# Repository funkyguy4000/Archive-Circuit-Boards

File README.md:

## This is an inactive repository used for archival purposes only
### Most of these designs and libraries were created while I was at university

#Circuit-Boards

A collection of my circuit boards and devices

##Strutz Library.lbr 
###This is a collection the parts I've made.  Some of the packages are copied from other libraries.
I'll list the important devices here:

Device | Package 1 | Package 2 | Package 3 | Description 
| --- | --- | --- | --- | --- |
**25AA1024**  |  DFN8-5x6 | 8-PDIP | SO8 | 1MBit SPI EEPROM from Microchip
**74AVC8T245** | QFN-60 | TSSOP-48 | | 8-biit logic level converter from NXP
**AD1939**  |  QFP64  | | | 4 ADC/ 8 DAC, 192 kHz, 24-Bit codec from Analog Devices
**ADP5589**  | 24-LFCSP (QFN) | 25-WLCSP (BGA) | | Keypad decoder / 19-bit IO Expander from Analog Devices
**ADSP-21479** | QFN-88 | | | SHARC DSP processor from Analog Devices
**ADSP-21483/6/7/9** | LQFP-176 | | | SHARC DSP processsor from analog devices
**AS1130** | TSSOP-28 | WL_CSP-20 (BGA) | | 132 LED driver from austriamicrosystems 
**AS3935** | QFN-16 | | | Lightning Sensor from austriamicrosystems
**AT25128B/256B** | 8VBGA | | | 128k/256k SPI EEPROM from Atmel
**ATMEGA8U2** | QFN-32 | | | 8-bit AVR microcontroller with embedded USB and 8kB flash from Atmel
**ATMEGA16** | 40-PDIP | | | 8-bit AVR microcontroller with 16kB flash from Atmel
**ATTINY4/5/6/9/10** | SOT-23-6 | | | 8-bit AVR micrcontroller for tiny applications from Atmel
**BGF120A** | TSLP-4-8 | | | Dual channel, ultra-low capacitance ESD diode from Infineon
**CS4234** | QFN-40 | | | 4 ADC/ 5 DAC Codec with programmable class H driver from Cirrus Logic
**CS4344** | TSSOP-10 | | | 24-bit, 192kHz Stereo DAC from Cirrus Logic
**CS5343** | TSSOP-10 | | | 24-bit Stereo ADC from Cirrus Logic
**CS42436** | QFP-52 | | | 6 ADC/ 6 DAC, 192kHz TDM audio codec from Cirrus Logic
**DS1077** | TSSOP-8 | | | Dual-programmable oscillator from Maxim
**FRDM-KL26Z**  | | | |  ***NOT TO BE USED FOR LAYOUT*** Only schematic purposes
**FT221X** | 20-QFN | 20-SSOP | | USB to FT1248 bridge from FTDI
**FT234XD** | DFN12-3x3 | | | USB to basic UART bridge from FTDI
**HIH-6130** | SO-8 | | | Digital humidity / temperature sensor from Honeywell
**HMC5983** | QFN-16 | | | 3-Axis digital compass from Honeywell
**L3GD20TR** | LGA-16 | | | 3-Axis digital gyroscope from ST Microelectronics
**LIS3MDL** | LGA-12 | | | 3-Axis digital magnetic sensor from ST Microelectronics
**LSM303DLHC** | LGA-14 | | | 3D accelerometer and 3D magnetometer from ST Microelectronics
**LT8500** | QFN-56 | | | 48-Channel LED PWM Generator with 12-bit resolution and 50MHz cascadeable serial interface from Linear Technologies
**LTC3539** | DFN8-3x3 | | | 2A, 1MHz/2MHz Synchronous Boost DC/DC Converter from Linear Technologies
**LTC3605** | QFN24 | | | 15V, 5A Synchronouse Buck Regulator from Linear Technologies
**LTC3811** | QFN38 | | | High Speed Dual, Multi-phase Buck DC/DC Controller from Linear Technologies
**M24M01** | BGA-8 | | | 1MBit I2C EEPROM from ST Microelectronics
**MCP2210** | QFN-20 | SSOP-20 | | USB to SPI bridge with GPIO from Microchip
**MMA8453Q** | QFN-16 | | | 3-Axis 10-bit/8-bit Digital Accelerometer from Freescale Semiconductor
**MMBT3904** | SOT-23 | | | 40V NPN small signal transistor
**MT48LC4M16A2** | TSOP-54 | | | 64MB x4 SDRAM from Micron
**OP275** | SO-8 | | | Bipolar/JFET Dual audio op-amp from Analog Devices
**PMOD** | 2x6 .1" Header | | | Custom part for PMOD breakout **UNTESTED**
**PT15** | 1206 | | | Phototransistor from Everlight
**RCA_Double** | Custom | | | Unkown
**SJ1-3514-SMT** | Custom | | |  Squarish Audio connector with tip switch from CUI Inc.  
**SJ3524** | Custom | | | Rectangular Audio connector with tip switch from CUI Inc
**TLC5940** | DIL28-3 | QFN-32 | TSSOP28-GROUNDPAD | 16-Channel LED driver with PWM control from Texas Instruments
**TLC5947** | QFN-32  | | | 24-Channel LED driver with PWM control from Texas Instruments
**TLC5958** | QFN-56 | | | 48-Channel LED driver with PWM control and 48kBit SRAM from Texas Instruments
**TPS62130A** | QFN16-3x3 | | | 3-17V 3A Buck DC/DC converter from Texas Instruments
**TPS84320** | RUQ_47(QFN) | | | 4.5-14.5V 3A Buck DC/DC converter from Texas Instruments
**TS3USB221** | 10-QFN | 10-SON  | | USB-2.0HS 1:2 Mux/Demux switch from Texas Instruments
**USB5534B** | QFN-64 | | | 4-Port SS/HS USB hub controller from Microchip
**USBA-DOUBLE** | Custom | | | Unknown
**WS2812-5050** | Custom | | | RGB LED driver with integrated WS2812 LED driver from Unknown
**XS1-L8A-128** | QFN-124 | | | 8-Core 32-Bit Microcontroller with 128kB SRAM from XMOS 
**XS1-U8A-128** | BGA-217 | | | 8-Core 32-Bit Microcontroller with USB Phy from XMOS
**XTAG-2** | MOLEX-52745-2097 | | | Proprietary debug adapter for XMOS devices

##On to the boards!

* **ADSP-21477...** - Breaks out the 88-QFN package of this DSP from Analog Devices
* **CS4344**  - Breaks out this Analog to Digital Converter from Cirrus
* **CS5343**  - Breaks out this Digital to Analog Converter from Cirrus
* **TLC5947 Old** - A board from when I used to layout without using a schematic.  Uses two TLC5947 ICs to manage 16 5050 RGB LEDS
* **Lego type WS2812** - A modular LED board made to connect to other pieces to make any LED display
* **Neopixel** - My board made after the Neopixel from Adafruit
* **Version 1 WS2812** - A square board using the WS2812 LEDs to make an LED matrix
* **Smod Boards** - These boards were made for half fun and half the University of Wisconsin - Stout IEEE
* **Stout IEEE Dev Board** - This is a development board in the form of an Arduino based off of the ATmega16 for UW-Stout IEEE.  Includes onboard programming based off of an ATtiny45.

More projects and such will be added soon.  I pretty much make a new one everyday.

<br />This work is licensed under a <a rel="license" href="http://creativecommons.org/licenses/by-sa/3.0/us/">Creative Commons Attribution-ShareAlike 3.0 United States License</a>.

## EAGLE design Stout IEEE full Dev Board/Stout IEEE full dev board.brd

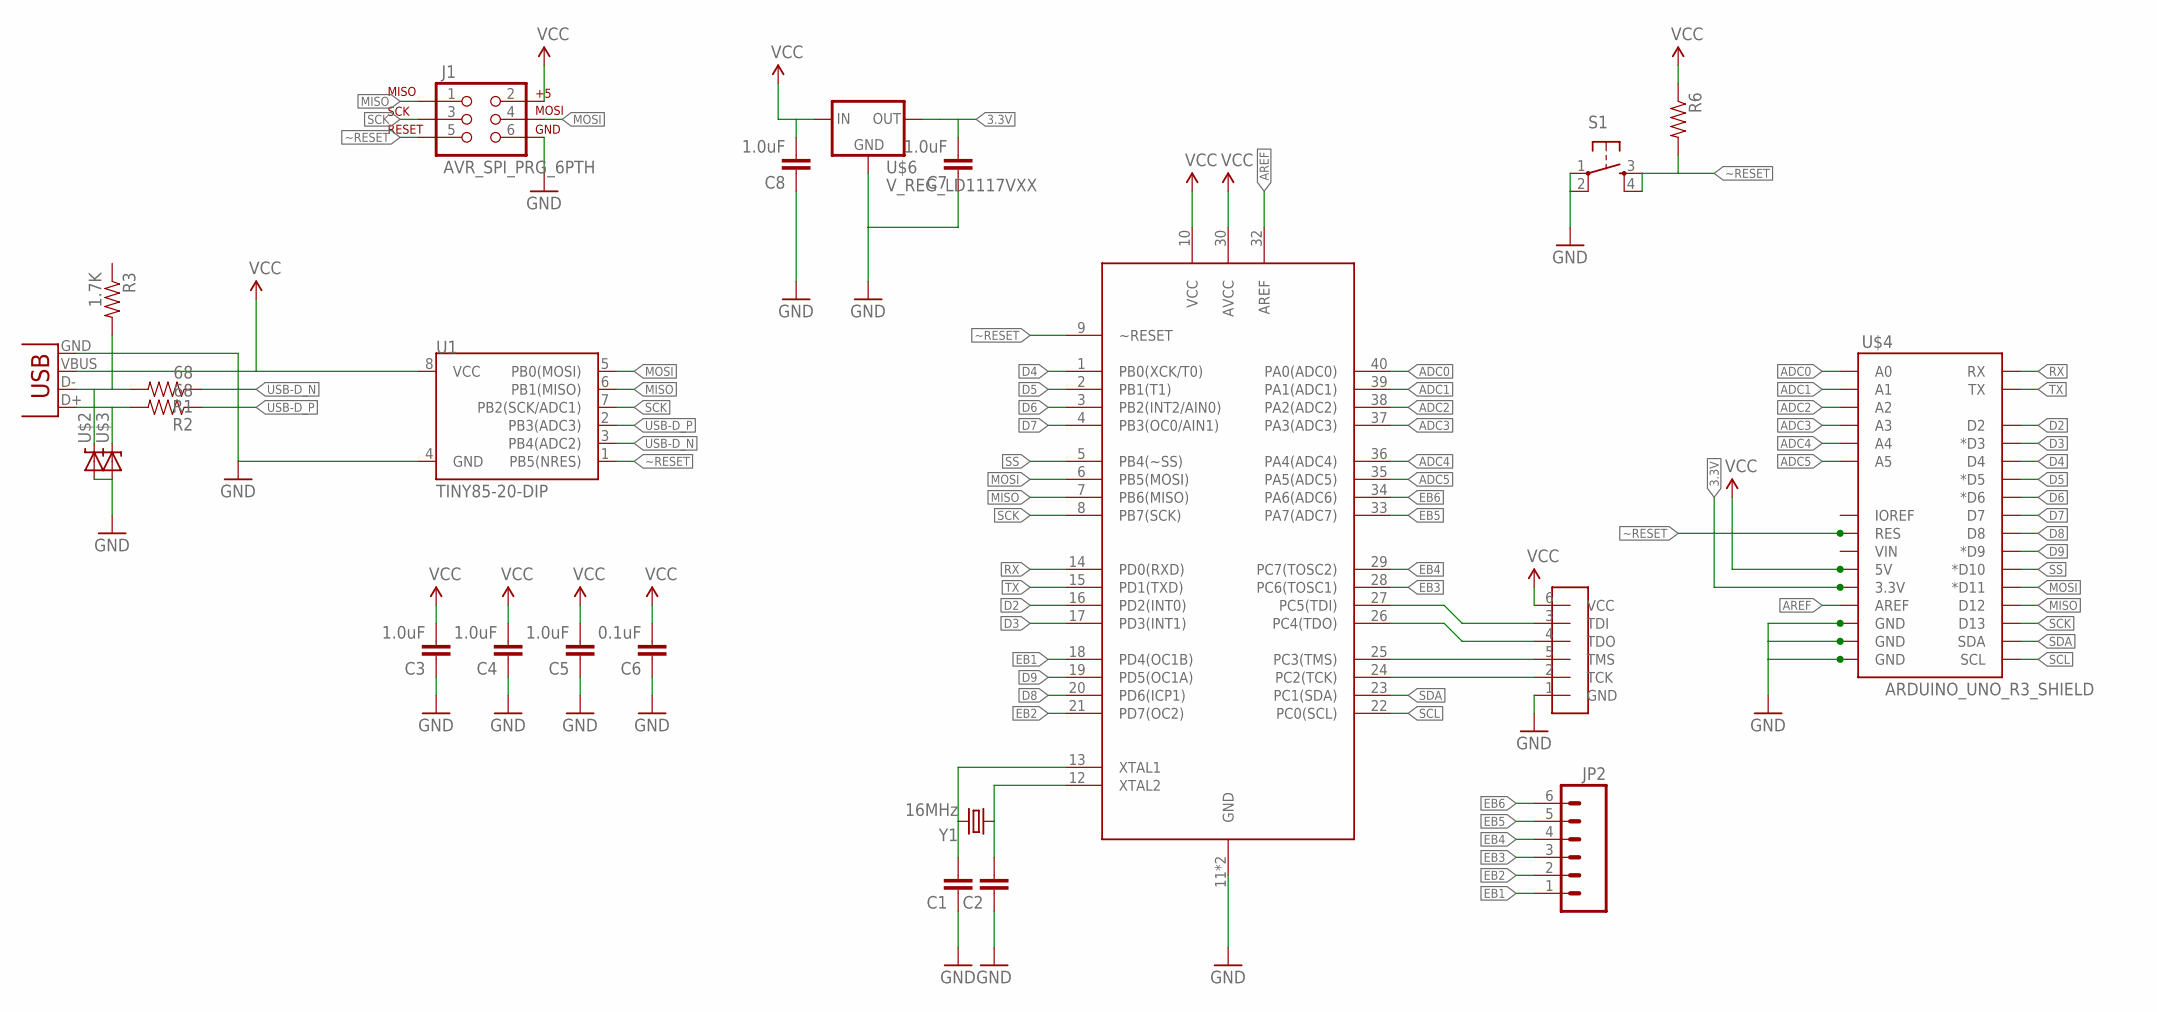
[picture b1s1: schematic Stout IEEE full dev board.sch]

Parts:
C1, C2: CAPPTH; CAP-PTH-SMALL
C3, C4, C5, C7, C8: 1.0uF; CAP-PTH-SMALL
C6: 0.1uF; CAP-PTH-SMALL
J1: AVR_SPI_PRG_6PTH; 2X3
JP1: USB-B; USB-B-PTH
JP2: M06SIP; 1X06
R1, R2: 68; AXIAL-0.4
R3: 1.7K; AXIAL-0.4
R6: RESISTORPTH-1/4W; AXIAL-0.4
S1: TAC_SWITCHPTH; TACTILE-PTH
U1: TINY85-20-DIP; DIP08
U$1: ATMEGA16DIP; 40-DIP
U$2, U$3: ZENER; DIODE-ZENER
U$4: ARDUINO_UNO_R3_SHIELD
U$5: JTAG; JTAG-FPC
U$6: V_REG_LD1117VXX; 78XXL
Y1: 16MHz; HC49US

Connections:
3.3V: C7.2, U$4.3.3V, U$6.GND (OUT)
ADC0: U$1.40 (PA0(ADC0)), U$4.A0
ADC1: U$1.39 (PA1(ADC1)), U$4.A1
ADC2: U$1.38 (PA2(ADC2)), U$4.A2
ADC3: U$1.37 (PA3(ADC3)), U$4.A3
ADC4: U$1.36 (PA4(ADC4)), U$4.A4
ADC5: U$1.35 (PA5(ADC5)), U$4.A5
AREF: U$1.32 (AREF), U$4.AREF
D2: U$1.16 (PD2(INT0)), U$4.D2
D3: U$1.17 (PD3(INT1)), U$4.D3 (*D3)
D4: U$1.1 (PB0(XCK/T0)), U$4.D4
D5: U$1.2 (PB1(T1)), U$4.D5 (*D5)
D6: U$1.3 (PB2(INT2/AIN0)), U$4.D6 (*D6)
D7: U$1.4 (PB3(OC0/AIN1)), U$4.D7
D8: U$1.20 (PD6(ICP1)), U$4.D8
D9: U$1.19 (PD5(OC1A)), U$4.D9 (*D9)
EB1: JP2.1, U$1.18 (PD4(OC1B))
EB2: JP2.2, U$1.21 (PD7(OC2))
EB3: JP2.3, U$1.28 (PC6(TOSC1))
EB4: JP2.4, U$1.29 (PC7(TOSC2))
EB5: JP2.5, U$1.33 (PA7(ADC7))
EB6: JP2.6, U$1.34 (PA6(ADC6))
GND: C1.1, C2.1, C3.1, C4.1, C5.1, C6.1, C7.1, C8.1, J1.6, JP1.GND, S1.1, S1.2, U1.4 (GND), U$1.11 (GND), U$1.31 (GND), U$2.P$2 (A), U$3.P$2 (A), U$4.GND@0 (GND), U$4.GND@1 (GND), U$4.GND@2 (GND), U$5.1 (GND), U$6.IN (GND)
MISO: J1.1, U1.6 (PB1(MISO)), U$1.7 (PB6(MISO)), U$4.D12
MOSI: J1.4, U1.5 (PB0(MOSI)), U$1.6 (PB5(MOSI)), U$4.D11 (*D11)
unnamed: C2.2, U$1.12 (XTAL2), Y1.1
unnamed: C1.2, U$1.13 (XTAL1), Y1.2
unnamed: JP1.D-, R1.P$2 (2), R3.P$2 (2), U$2.P$1 (C)
unnamed: JP1.D+, R2.P$2 (2), U$3.P$1 (C)
unnamed: U$1.24 (PC2(TCK)), U$5.2 (TCK)
unnamed: U$1.25 (PC3(TMS)), U$5.5 (TMS)
unnamed: U$1.26 (PC4(TDO)), U$5.4 (TDO)
unnamed: U$1.27 (PC5(TDI)), U$5.3 (TDI)
RX: U$1.14 (PD0(RXD)), U$4.RX
SCK: J1.3, U1.7 (PB2(SCK/ADC1)), U$1.8 (PB7(SCK)), U$4.D13
SCL: U$1.22 (PC0(SCL)), U$4.SCL
SDA: U$1.23 (PC1(SDA)), U$4.SDA
SS: U$1.5 (PB4(~SS)), U$4.D10 (*D10)
TX: U$1.15 (PD1(TXD)), U$4.TX
USB-D_N: R1.P$1 (1), U1.3 (PB4(ADC2))
USB-D_P: R2.P$1 (1), U1.2 (PB3(ADC3))
VCC: C3.2, C4.2, C5.2, C6.2, C8.2, J1.2, JP1.VBUS, R6.P$1 (1), U1.8 (VCC), U$1.10 (VCC), U$1.30 (AVCC), U$4.5V, U$5.6 (VCC), U$6.OUT (IN)
~RESET: J1.5, R6.P$2 (2), S1.3, S1.4, U1.1 (PB5(NRES)), U$1.9 (~RESET), U$4.RES

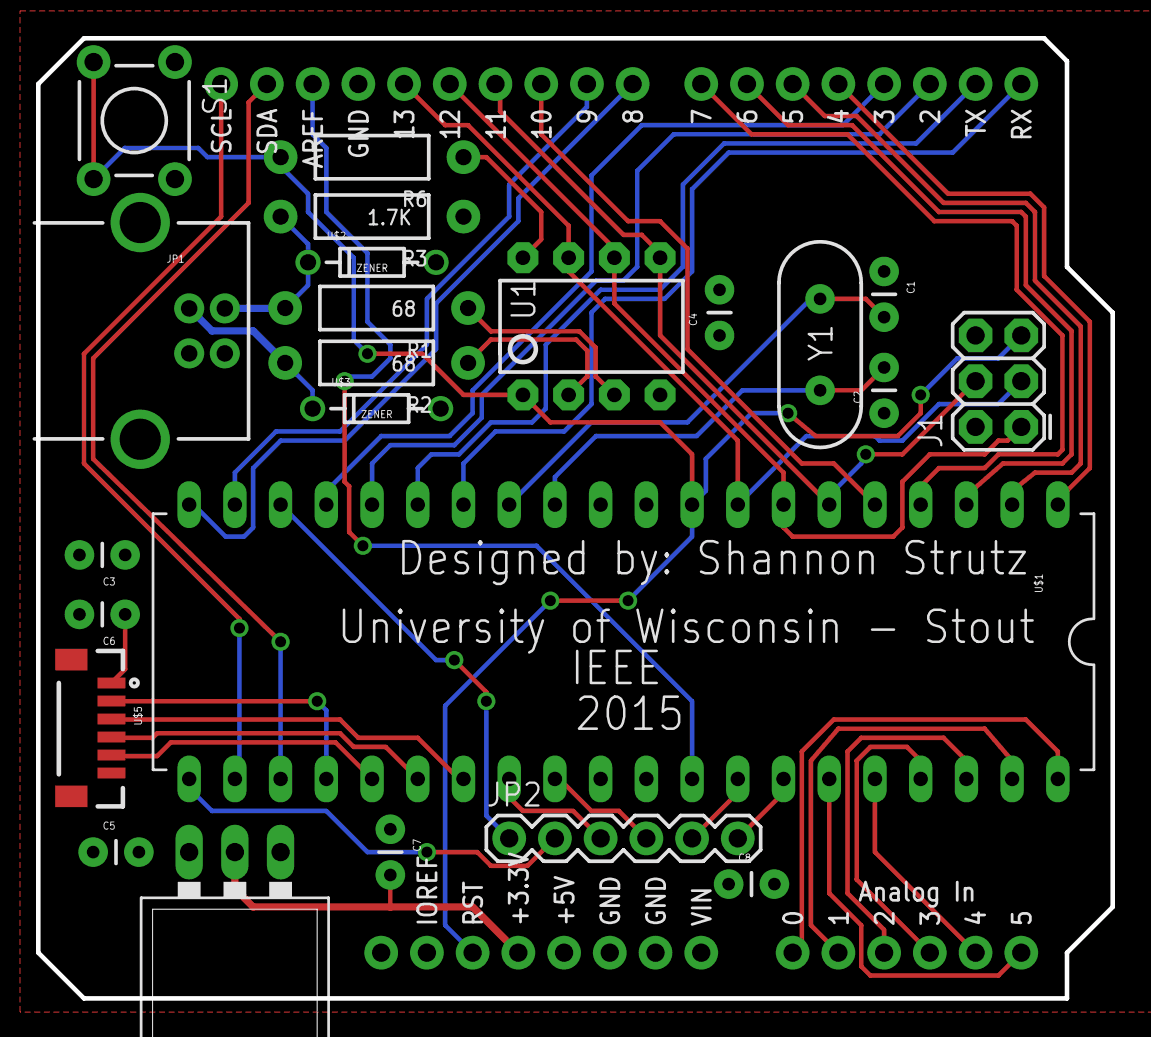
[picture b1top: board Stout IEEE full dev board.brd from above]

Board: 2 copper layers, 59.7 x 53.3 mm, 24 parts (0 on the bottom side), 43 nets.

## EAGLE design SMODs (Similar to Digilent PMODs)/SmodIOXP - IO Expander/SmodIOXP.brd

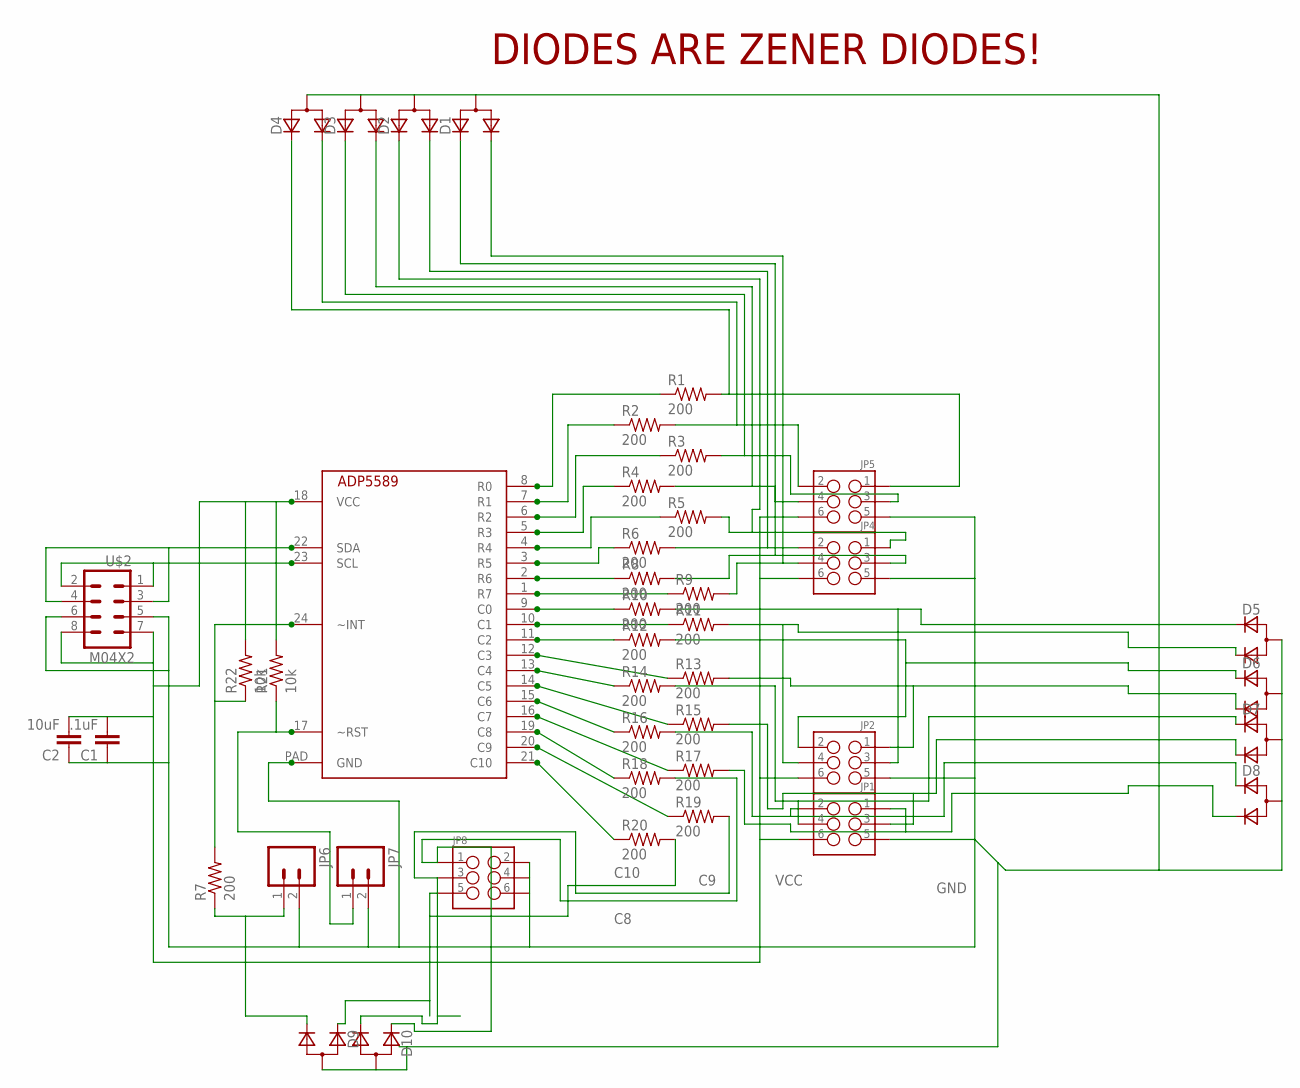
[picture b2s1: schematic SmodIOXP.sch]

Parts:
C1: .1uF; 0603-CAP
C2: 10uF; 0603-CAP
D1, D2, D3, D4, D5, D6, D7, D8, D9, D10: D_2CSOT23; SOT-23
JP1, JP2, JP4, JP5, JP8: M03X2POGO_PINS; 2X3_POGO
JP6, JP7: M02PTH; 1X02
R1, R2, R3, R4, R5, R6, R7, R8, R9, R10, R11, R12, R13, R14, R15, R16, R17, R18, R19, R20: 200; 0603-RES
R21, R22: 10k; 0603-RES
U$1: ADP5589LFCSP(QFN); 24-LFCSP
U$2: M04X2; 2X4

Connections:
C0: D5.2 (C1), JP2.P$3 (3), R10.2
C1: D5.3 (C2), JP2.P$4 (4), R11.2
C2: D6.2 (C1), JP2.P$2 (2), R12.2
C3: D6.3 (C2), JP2.P$1 (1), R13.2
C4: D7.2 (C1), JP1.P$4 (4), R14.2
C5: D7.3 (C2), JP1.P$3 (3), R15.2
C6: D8.2 (C1), JP1.P$2 (2), R16.2
C7: D8.3 (C2), JP1.P$1 (1), R17.2
C8: D10.2 (C1), JP8.P$1 (1), R18.2
C9: D10.3 (C2), JP8.P$3 (3), R19.2
C10: D9.2 (C1), JP8.P$5 (5), R20.2
GND: C1.1, C2.1, D1.1 (A), D2.1 (A), D3.1 (A), D4.1 (A), D5.1 (A), D6.1 (A), D7.1 (A), D8.1 (A), D9.1 (A), D10.1 (A), JP1.P$5 (5), JP2.P$5 (5), JP4.P$5 (5), JP5.P$5 (5), JP6.2, JP7.2, JP8.P$2 (2), JP8.P$4 (4), JP8.P$6 (6), U$1.PAD (GND), U$2.5, U$2.6
unnamed: R1.1, U$1.8 (R0)
unnamed: R2.1, U$1.7 (R1)
unnamed: R3.1, U$1.6 (R2)
unnamed: D9.3 (C2), JP6.1, R7.1
unnamed: R4.1, U$1.5 (R3)
unnamed: R5.1, U$1.4 (R4)
unnamed: R6.1, U$1.3 (R5)
unnamed: R8.1, U$1.2 (R6)
unnamed: R9.1, U$1.1 (R7)
unnamed: R10.1, U$1.9 (C0)
unnamed: R11.1, U$1.10 (C1)
unnamed: R12.1, U$1.11 (C2)
unnamed: R13.1, U$1.12 (C3)
unnamed: R14.1, U$1.13 (C4)
unnamed: R15.1, U$1.14 (C5)
unnamed: R16.1, U$1.15 (C6)
unnamed: R17.1, U$1.16 (C7)
unnamed: R18.1, U$1.19 (C8)
unnamed: R19.1, U$1.20 (C9)
unnamed: R20.1, U$1.21 (C10)
R0: D4.2 (C1), JP5.P$1 (1), R1.2
R1: D4.3 (C2), JP5.P$2 (2), R2.2
R2: D3.2 (C1), JP5.P$3 (3), R3.2
R3: D3.3 (C2), JP5.P$4 (4), R4.2
R4: D2.2 (C1), JP4.P$1 (1), R5.2
R5: D2.3 (C2), JP4.P$2 (2), R6.2
R6: D1.2 (C1), JP4.P$3 (3), R8.2
R7: D1.3 (C2), JP4.P$4 (4), R9.2
SCL: U$1.23 (SCL), U$2.1, U$2.2
SDA: U$1.22 (SDA), U$2.3, U$2.4
VCC: C1.2, C2.2, JP1.P$6 (6), JP2.P$6 (6), JP4.P$6 (6), JP5.P$6 (6), R21.2, R22.2, U$1.18 (VCC), U$2.7, U$2.8
~INT: R7.2, R22.1, U$1.24 (~INT)
~RST: JP7.1, R21.1, U$1.17 (~RST)

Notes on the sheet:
DIODES ARE ZENER DIODES!

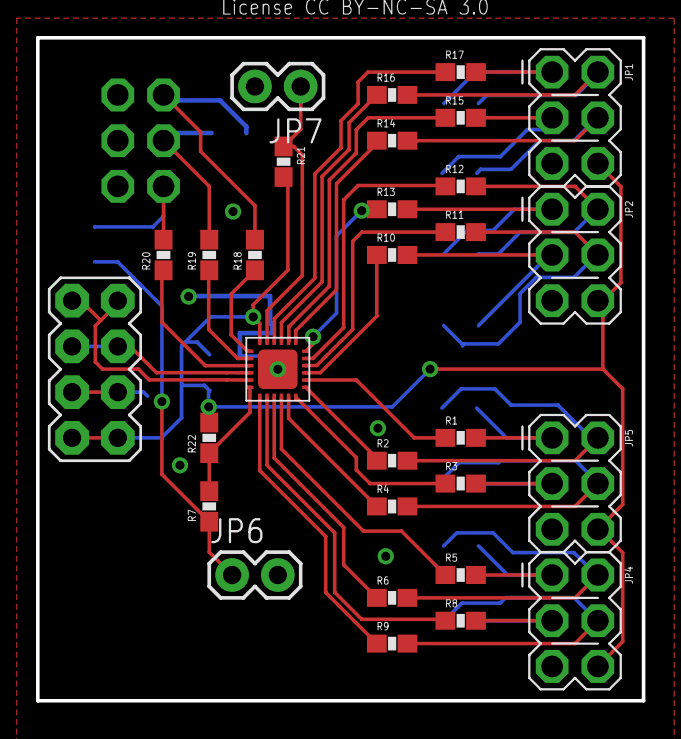
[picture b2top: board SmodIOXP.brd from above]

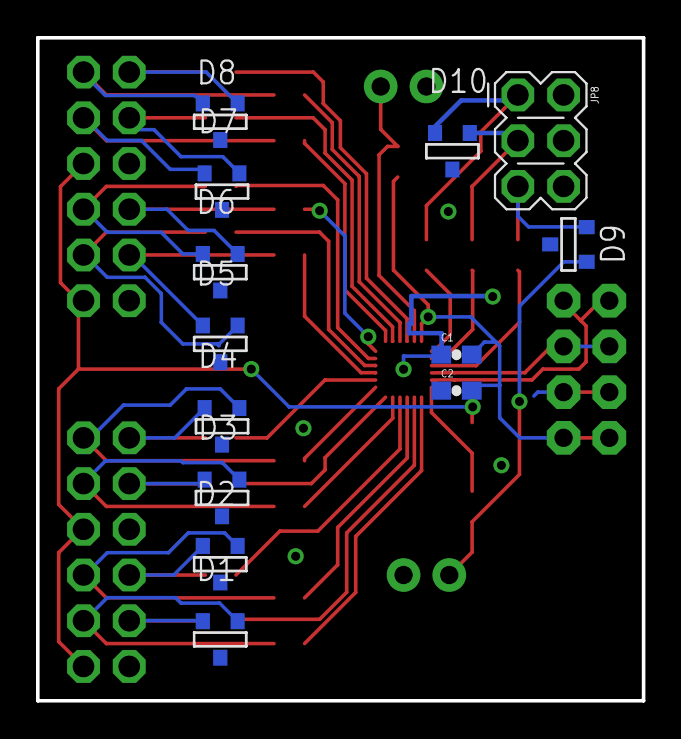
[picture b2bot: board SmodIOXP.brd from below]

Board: 2 copper layers, 33.7 x 36.8 mm, 43 parts (13 on the bottom side), 45 nets.

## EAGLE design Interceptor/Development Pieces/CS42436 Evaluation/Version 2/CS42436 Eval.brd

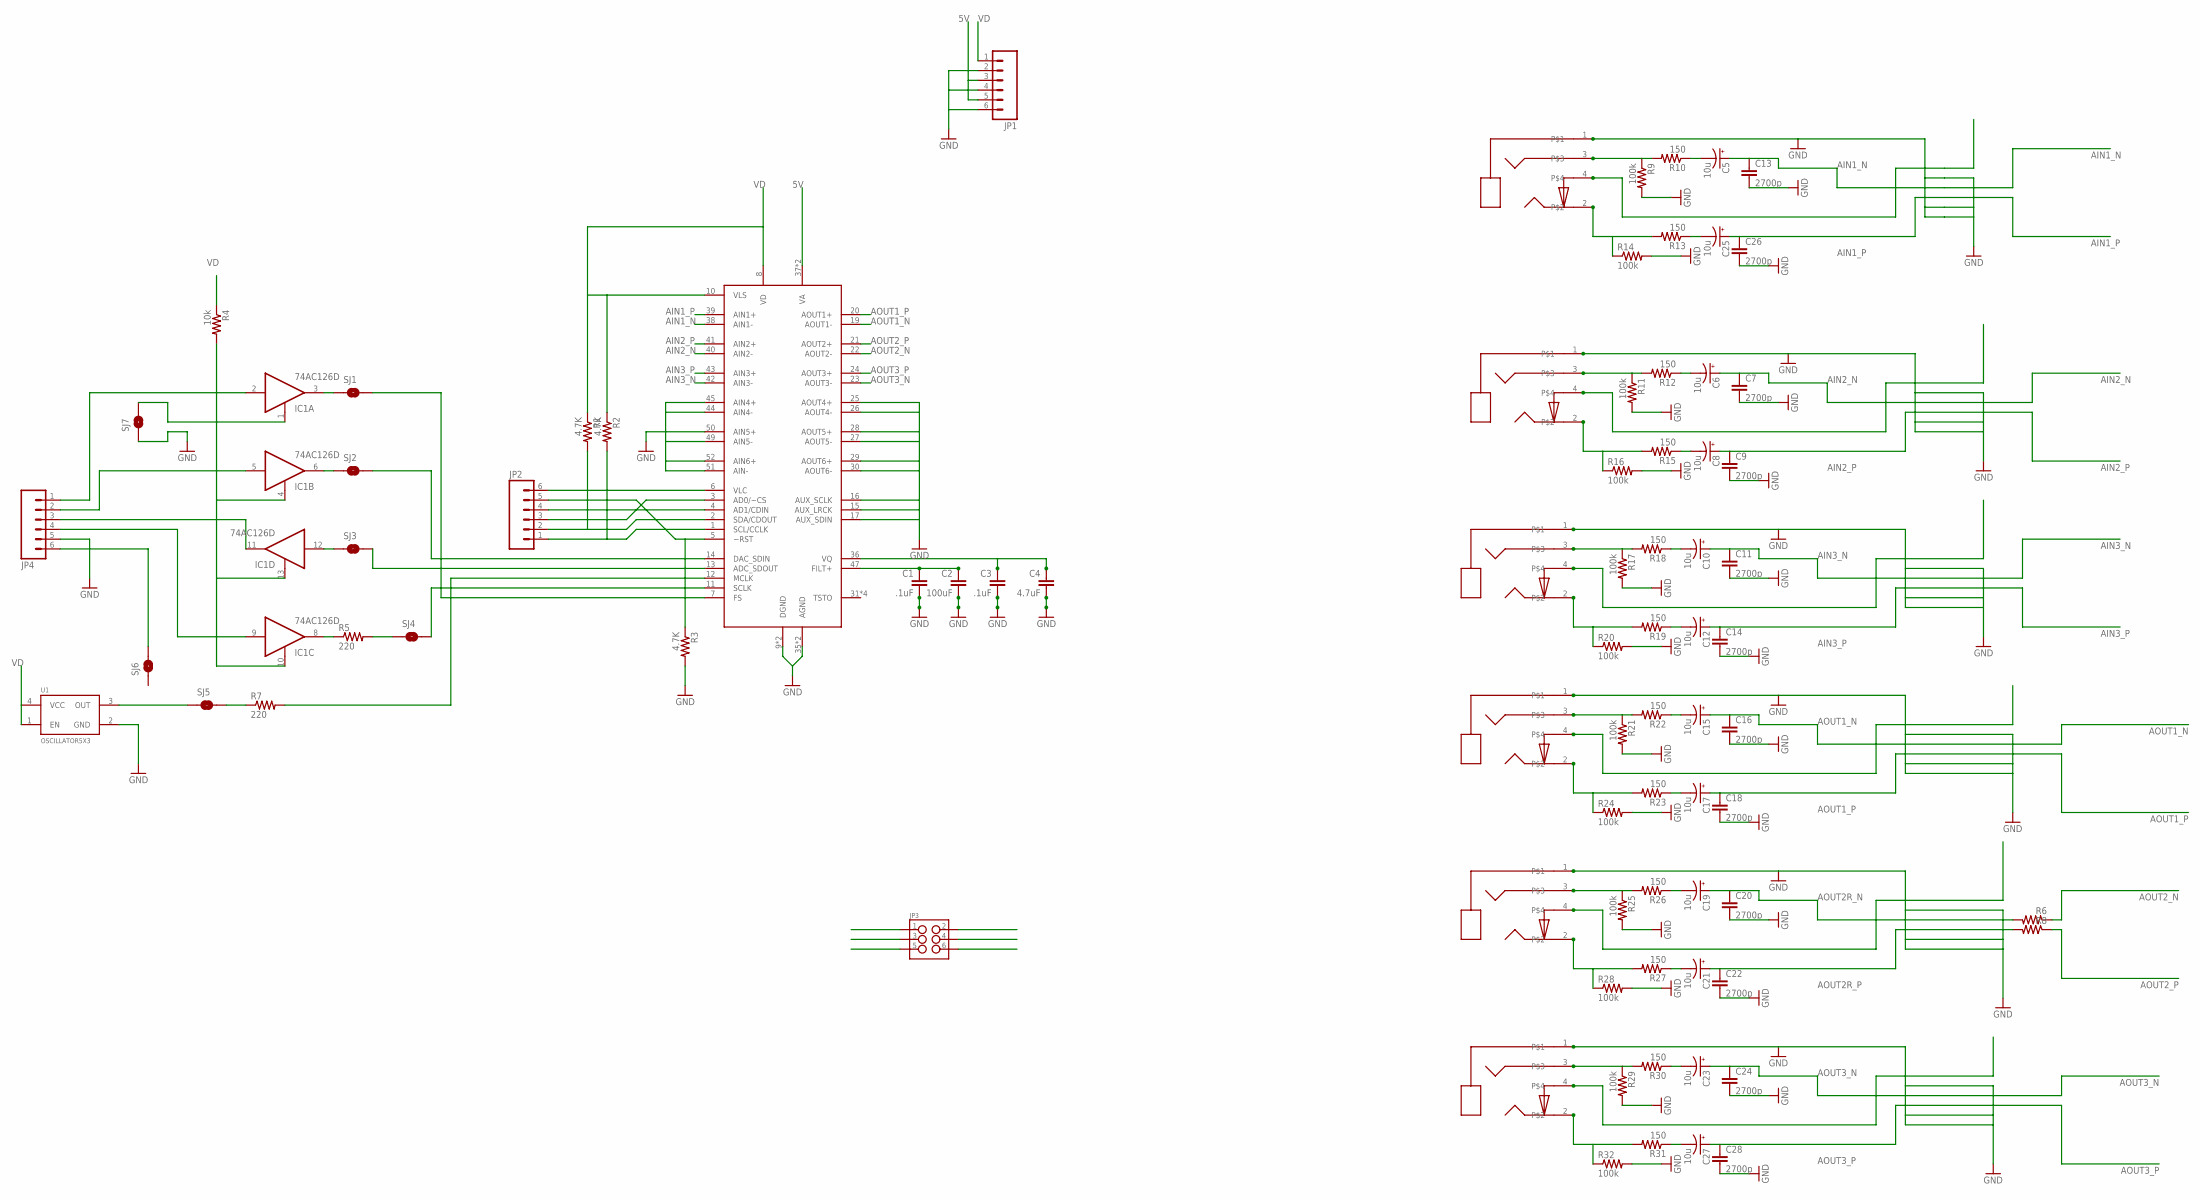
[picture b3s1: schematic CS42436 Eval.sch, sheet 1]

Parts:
C1, C3: .1uF; 0603-CAP
C2: 100uF; 1206
C4: 4.7uF; 1206
C5, C6, C8, C10, C12, C15, C17, C19, C21, C23, C25, C27: 10u; PANASONIC_B
C7, C9, C11, C13, C14, C16, C18, C20, C22, C24, C26, C28: 2700p; 0603-CAP
IC1: 74AC126D; SO14
J1, J2, J3, J4, J5, J6: SJ1-3514-SMT
JP1: M06SMD; 1X06-SMD
JP2, JP4: M06SIP; 1X06
JP3: M03X2NO_SILK; 2X3-NS
R1, R2, R3: 4.7K; 0603-RES
R4: 10k; 0603-RES
R5, R7: 220; 0603-RES
R6, R8: RESISTOR1206; 1206
R9, R11, R14, R16, R17, R20, R21, R24, R25, R28, R29, R32: 100k; 0603-RES
R10, R12, R13, R15, R18, R19, R22, R23, R26, R27, R30, R31: 150; 0603-RES
SJ1, SJ2, SJ3, SJ4, SJ5, SJ6, SJ7: SOLDERJUMPERTRACE; SJ_2S-TRACE
U1: OSCILLATOR5X3; CRYSTAL-SMD-5X3
U$1: CS42436; QFP-52

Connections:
5V: JP1.3, JP1.5, U$1.37 (VA), U$1.46 (VA)
AIN1_N: C5.+, C13.1, U$1.38 (AIN1-)
AIN1_P: C25.+, C26.1, U$1.39 (AIN1+)
AIN2_N: C6.+, C7.1, U$1.40 (AIN2-)
AIN2_P: C8.+, C9.1, U$1.41 (AIN2+)
AIN3_N: C10.+, C11.1, U$1.42 (AIN3-)
AIN3_P: C12.+, C14.1, U$1.43 (AIN3+)
AOUT1_N: C15.+, C16.1, U$1.19 (AOUT1-)
AOUT1_P: C17.+, C18.1, U$1.20 (AOUT1+)
AOUT2R_N: C19.+, C20.1, R6.2
AOUT2R_P: C21.+, C22.1, R8.2
AOUT2_N: R6.1, U$1.22 (AOUT2-)
AOUT2_P: R8.1, U$1.21 (AOUT2+)
AOUT3_N: C23.+, C24.1, U$1.23 (AOUT3-)
AOUT3_P: C27.+, C28.1, U$1.24 (AOUT3+)
CH1_IN: J1.4, JP3.1
CH1_OUT: J4.4, JP3.2
CH2_IN: J2.4, JP3.3
CH2_OUT: J5.4, JP3.4
CH3_IN: J3.4, JP3.5
CH3_OUT: J6.4, JP3.6
GND: C1.2, C2.2, C3.2, C4.2, C7.2, C9.2, C11.2, C13.2, C14.2, C16.2, C18.2, C20.2, C22.2, C24.2, C26.2, C28.2, IC1.7 (GND), J1.1, J2.1, J3.1, J4.1, J5.1, J6.1, JP1.2, JP1.4, JP1.6, JP4.5, R3.2, R9.2, R11.2, R14.2, R16.2, R17.2, R20.2, R21.2, R24.2, R25.2, R28.2, R29.2, R32.2, SJ7.1, U1.2 (GND), U$1.9 (DGND), U$1.15 (AUX_LRCK), U$1.16 (AUX_SCLK), U$1.17 (AUX_SDIN), U$1.18 (DGND), U$1.25 (AOUT4+), U$1.26 (AOUT4-), U$1.27 (AOUT5-), U$1.28 (AOUT5+), U$1.29 (AOUT6+), U$1.30 (AOUT6-), U$1.35 (AGND), U$1.44 (AIN4-), U$1.45 (AIN4+), U$1.48 (AGND), U$1.49 (AIN5-), U$1.50 (AIN5+), U$1.51 (AIN-), U$1.52 (AIN6+)
unnamed: C1.1, C2.1, U$1.47 (FILT+)
unnamed: C3.1, C4.1, U$1.36 (VQ)
unnamed: SJ1.2, U$1.7 (FS)
unnamed: IC1.6 (O), SJ2.1
unnamed: IC1.2 (I), JP4.1
unnamed: IC1.1 (OE), IC1.4 (OE), IC1.10 (OE), IC1.13 (OE), R4.2, SJ7.2
unnamed: R7.1, SJ5.2
unnamed: IC1.11 (O), JP4.3
unnamed: IC1.5 (I), JP4.2
unnamed: IC1.12 (I), SJ3.1
unnamed: IC1.3 (O), SJ1.1
unnamed: SJ2.2, U$1.14 (DAC_SDIN)
unnamed: J1.3, R9.1, R10.2
unnamed: SJ3.2, U$1.13 (ADC_SDOUT)
unnamed: JP2.1, R2.2, U$1.1 (SCL/CCLK)
unnamed: JP2.2, R1.2, U$1.2 (SDA/CDOUT)
unnamed: JP2.3, U$1.3 (AD0/~CS)
unnamed: C5.-, R10.1
unnamed: JP2.4, U$1.4 (AD1/CDIN)
unnamed: JP2.5, R3.1, U$1.5 (~RST)
unnamed: JP2.6, U$1.6 (VLC)
unnamed: IC1.8 (O), R5.1
unnamed: R5.2, SJ4.1
unnamed: SJ4.2, U$1.11 (SCLK)
unnamed: J2.3, R11.1, R12.2
unnamed: C25.-, R13.1
unnamed: R7.2, U$1.12 (MCLK)
unnamed: IC1.9 (I), JP4.4
unnamed: SJ5.1, U1.3 (OUT)
unnamed: JP4.6, SJ6.2
unnamed: J1.2, R13.2, R14.1
unnamed: C6.-, R12.1
unnamed: C8.-, R15.1
unnamed: J2.2, R15.2, R16.1
unnamed: J3.3, R17.1, R18.2
unnamed: C10.-, R18.1
unnamed: C12.-, R19.1
unnamed: J3.2, R19.2, R20.1
unnamed: J4.3, R21.1, R22.2
unnamed: C15.-, R22.1
unnamed: C17.-, R23.1
unnamed: J4.2, R23.2, R24.1
unnamed: J5.3, R25.1, R26.2
unnamed: C19.-, R26.1
unnamed: C21.-, R27.1
unnamed: J5.2, R27.2, R28.1
unnamed: J6.3, R29.1, R30.2
unnamed: C23.-, R30.1
unnamed: C27.-, R31.1
unnamed: J6.2, R31.2, R32.1
VCC: IC1.14 (VCC)
VD: JP1.1, R1.1, R2.1, R4.1, U1.1 (EN), U1.4 (VCC), U$1.8 (VD), U$1.10 (VLS)

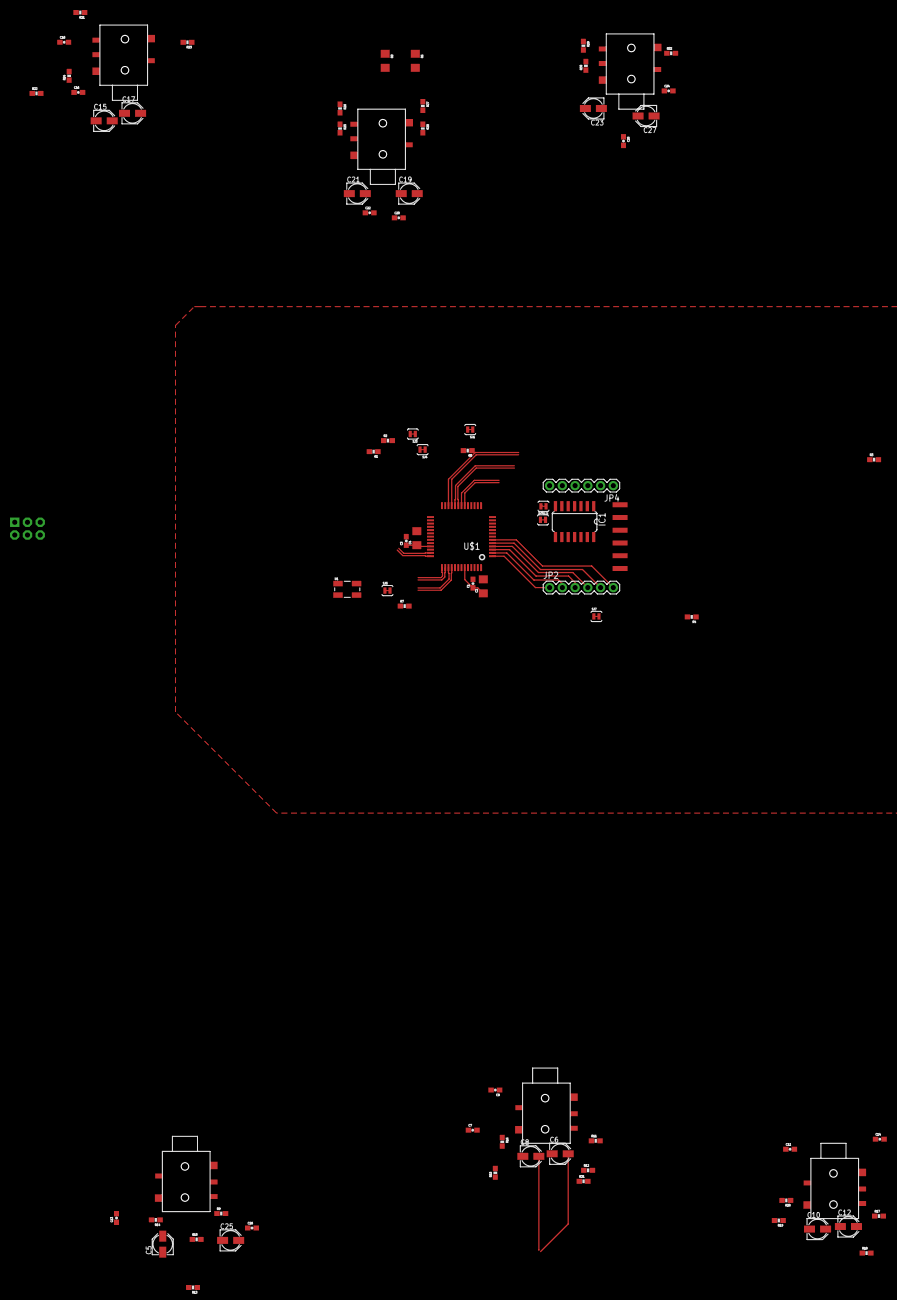
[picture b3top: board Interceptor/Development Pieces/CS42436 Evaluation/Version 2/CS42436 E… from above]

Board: 2 copper layers, 80 parts (1 on the bottom side), 73 nets.

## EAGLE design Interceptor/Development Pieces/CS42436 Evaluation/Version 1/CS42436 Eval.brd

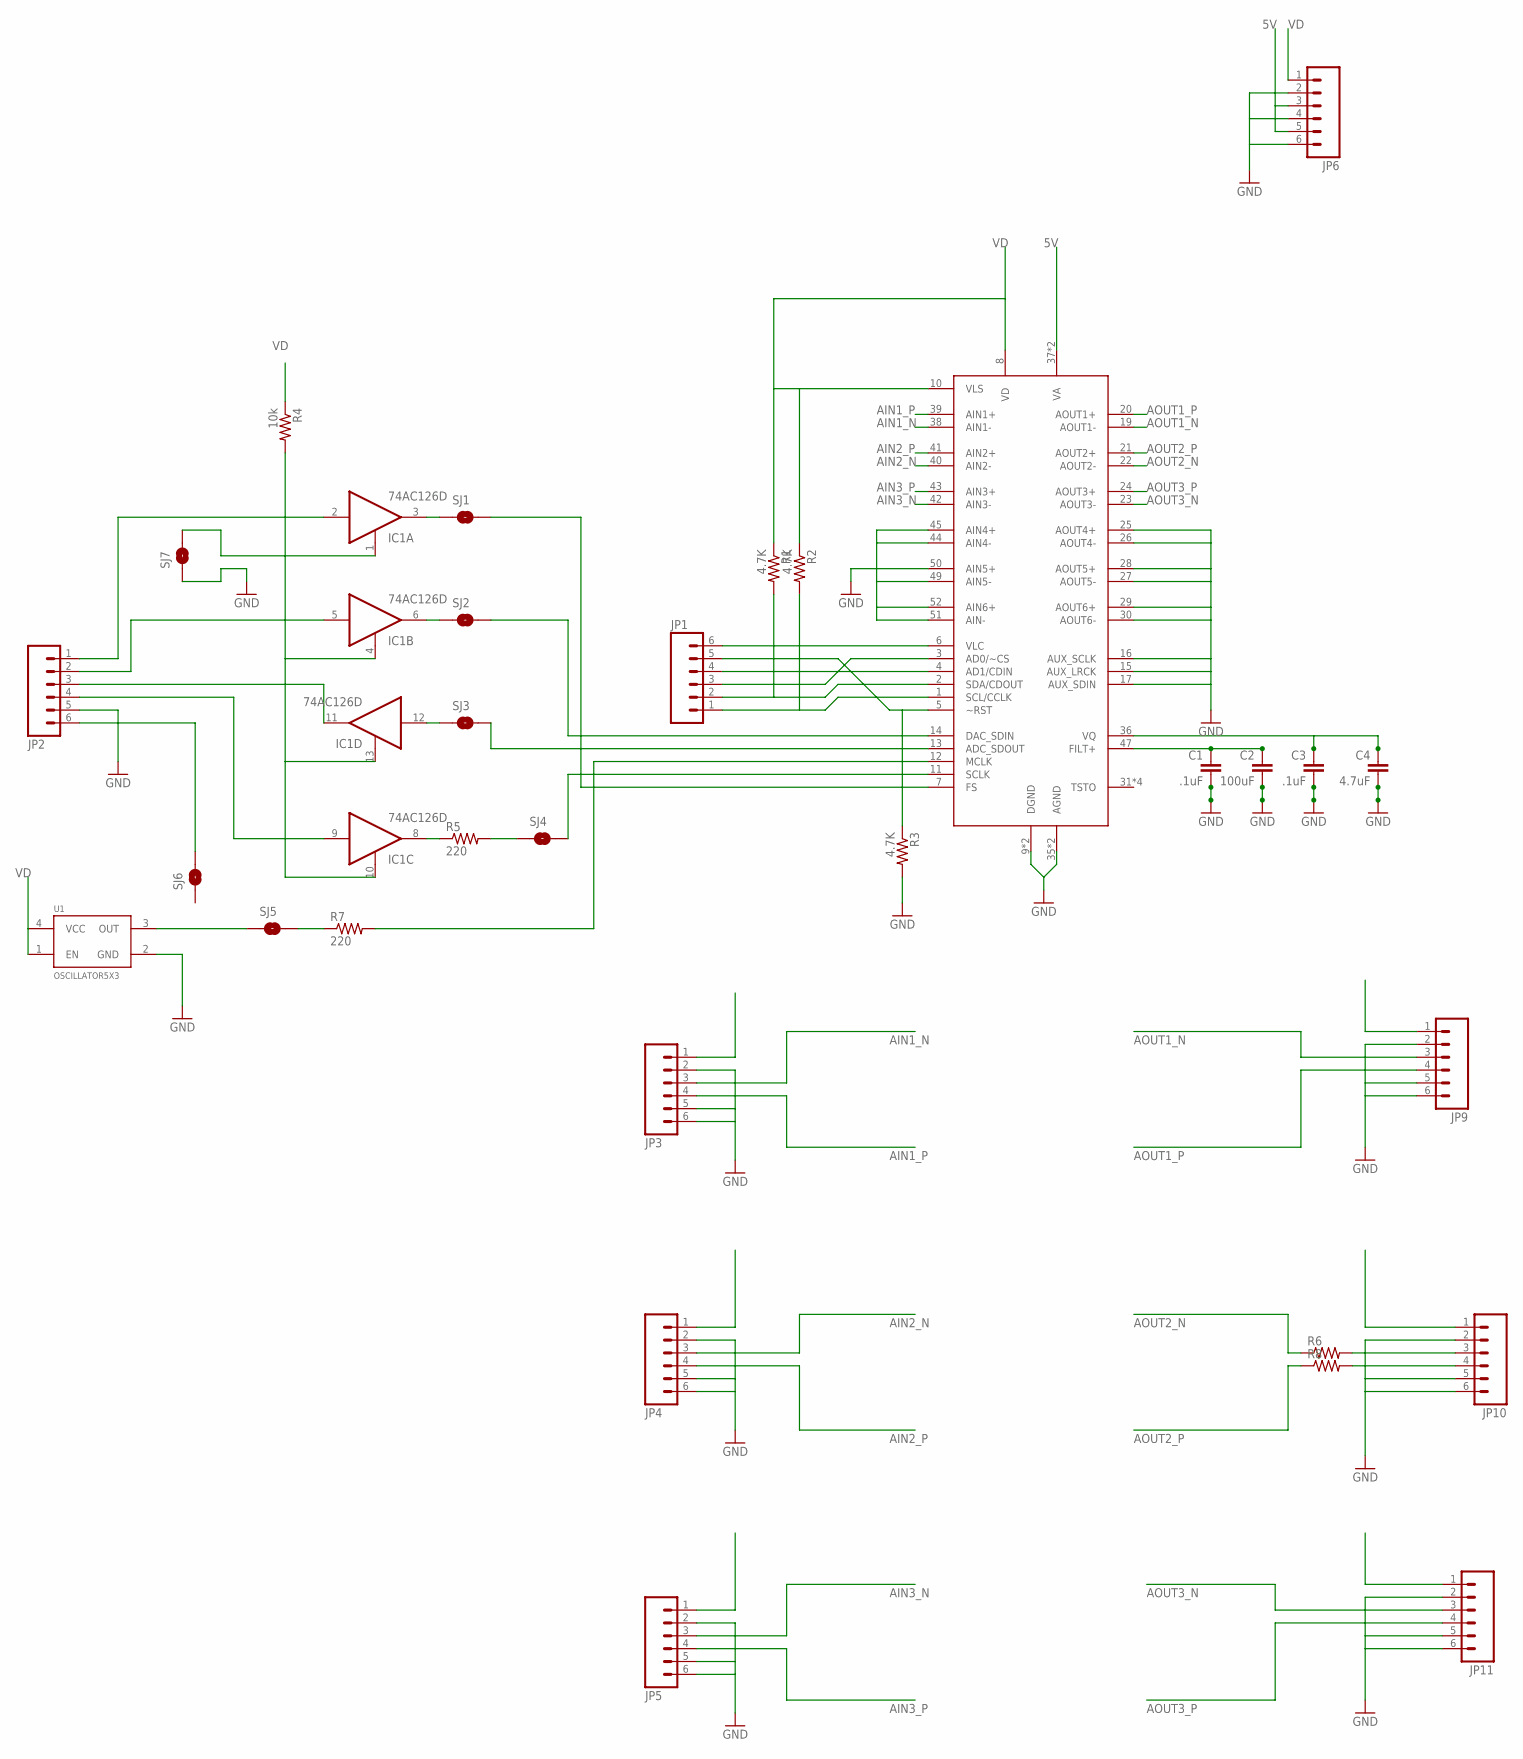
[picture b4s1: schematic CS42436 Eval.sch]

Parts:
C1, C3: .1uF; 0603-CAP
C2: 100uF; 0603-CAP
C4: 4.7uF; 0603-CAP
IC1: 74AC126D; SO14
JP1, JP2, JP3, JP4, JP5, JP9, JP10, JP11: M06SMD; 1X06-SMD
JP6: M06SMD-STRAIGHT-ALT; 1X06_SMD_STRAIGHT_ALT
R1, R2, R3: 4.7K; R0402
R4: 10k; R0402
R5, R7: 220; R0402
R6, R8: RESISTOR1206; 1206
SJ1, SJ2, SJ3, SJ4, SJ5, SJ6, SJ7: SOLDERJUMPERTRACE; SJ_2S-TRACE
U1: OSCILLATOR5X3; CRYSTAL-SMD-5X3
U$1: CS42436; QFP-52

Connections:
5V: JP6.3, JP6.5, U$1.37 (VA), U$1.46 (VA)
AIN1_N: JP3.3, U$1.38 (AIN1-)
AIN1_P: JP3.4, U$1.39 (AIN1+)
AIN2_N: JP4.3, U$1.40 (AIN2-)
AIN2_P: JP4.4, U$1.41 (AIN2+)
AIN3_N: JP5.3, U$1.42 (AIN3-)
AIN3_P: JP5.4, U$1.43 (AIN3+)
AOUT1_N: JP9.3, U$1.19 (AOUT1-)
AOUT1_P: JP9.4, U$1.20 (AOUT1+)
AOUT2_N: R6.1, U$1.22 (AOUT2-)
AOUT2_NR: JP10.3, R6.2
AOUT2_P: R8.1, U$1.21 (AOUT2+)
AOUT3_N: JP11.3, U$1.23 (AOUT3-)
AOUT3_P: JP11.4, U$1.24 (AOUT3+)
AOUT_2PN: JP10.4, R8.2
GND: C1.2, C2.2, C3.2, C4.2, IC1.7 (GND), JP2.5, JP3.2, JP3.5, JP3.6, JP4.2, JP4.5, JP4.6, JP5.2, JP5.5, JP5.6, JP6.2, JP6.4, JP6.6, JP9.2, JP9.5, JP9.6, JP10.2, JP10.5, JP10.6, JP11.2, JP11.5, JP11.6, R3.2, SJ7.1, U1.2 (GND), U$1.9 (DGND), U$1.15 (AUX_LRCK), U$1.16 (AUX_SCLK), U$1.17 (AUX_SDIN), U$1.18 (DGND), U$1.25 (AOUT4+), U$1.26 (AOUT4-), U$1.27 (AOUT5-), U$1.28 (AOUT5+), U$1.29 (AOUT6+), U$1.30 (AOUT6-), U$1.35 (AGND), U$1.44 (AIN4-), U$1.45 (AIN4+), U$1.48 (AGND), U$1.49 (AIN5-), U$1.50 (AIN5+), U$1.51 (AIN-), U$1.52 (AIN6+)
unnamed: C1.1, C2.1, U$1.47 (FILT+)
unnamed: C3.1, C4.1, U$1.36 (VQ)
unnamed: SJ1.2, U$1.7 (FS)
unnamed: IC1.6 (O), SJ2.1
unnamed: IC1.2 (I), JP2.1
unnamed: IC1.1 (OE), IC1.4 (OE), IC1.10 (OE), IC1.13 (OE), R4.2, SJ7.2
unnamed: R7.1, SJ5.2
unnamed: IC1.11 (O), JP2.3
unnamed: IC1.5 (I), JP2.2
unnamed: IC1.12 (I), SJ3.1
unnamed: IC1.3 (O), SJ1.1
unnamed: SJ2.2, U$1.14 (DAC_SDIN)
unnamed: SJ3.2, U$1.13 (ADC_SDOUT)
unnamed: JP1.1, R2.2, U$1.1 (SCL/CCLK)
unnamed: JP1.2, R1.2, U$1.2 (SDA/CDOUT)
unnamed: JP1.3, U$1.3 (AD0/~CS)
unnamed: JP1.4, U$1.4 (AD1/CDIN)
unnamed: JP1.5, R3.1, U$1.5 (~RST)
unnamed: JP1.6, U$1.6 (VLC)
unnamed: IC1.8 (O), R5.1
unnamed: R5.2, SJ4.1
unnamed: SJ4.2, U$1.11 (SCLK)
unnamed: R7.2, U$1.12 (MCLK)
unnamed: IC1.9 (I), JP2.4
unnamed: SJ5.1, U1.3 (OUT)
unnamed: JP2.6, SJ6.2
VCC: IC1.14 (VCC)
VD: JP6.1, R1.1, R2.1, R4.1, U1.1 (EN), U1.4 (VCC), U$1.8 (VD), U$1.10 (VLS)

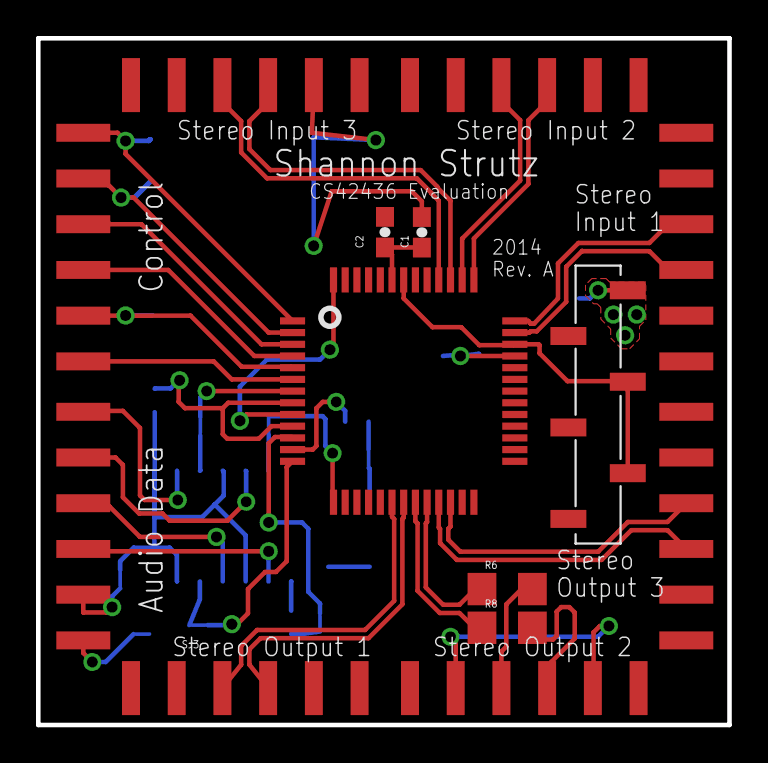
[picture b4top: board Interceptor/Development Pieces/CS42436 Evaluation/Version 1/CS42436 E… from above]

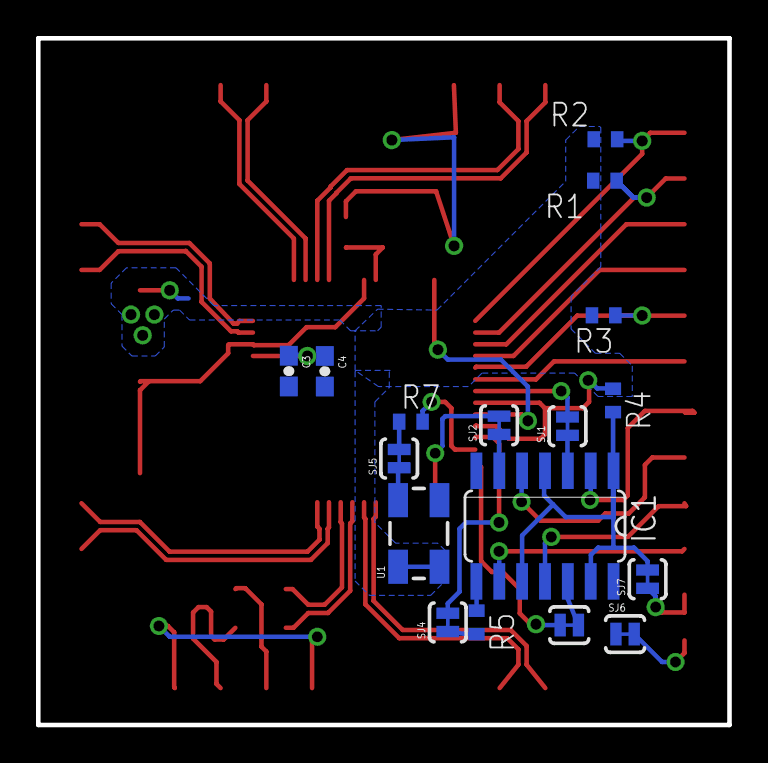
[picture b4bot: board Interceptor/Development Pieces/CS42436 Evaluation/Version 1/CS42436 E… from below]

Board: 2 copper layers, 38.4 x 38.1 mm, 31 parts (17 on the bottom side), 43 nets.

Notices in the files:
SMODs (Similar to Digilent PMODs)/SmodIOXP - IO Expander/SmodIOXP.brd:
License CC BY-NC-SA 3.0
parts and their libraries:
SparkFun-Connectors: Licensing: CC v3.0 Share-Alike You are welcome to use this library for commercial purposes.
